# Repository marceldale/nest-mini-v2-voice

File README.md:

# Open voice satellite board for the Google Nest Mini (2nd gen)

A drop-in replacement board that turns a Google Nest Mini (2nd gen) into a fully local voice
assistant for Home Assistant. Started from the open design by
[iMike78](https://github.com/iMike78/nest-mini-drop-in-pcb) (nest-mini-drop-in-pcb,
CERN-OHL-S v2) and since then reworked, verified and extended into its own board. Everything
that was changed, and why, is in [CHANGES.md](CHANGES.md); the people and projects this one
stands on are named under [Credits](#credits).

> [!WARNING]
> **Status (5 Oct 2026): rev A2 in production at JLCPCB (2 boards, ordered 2 Oct 2026, completion
> expected around 14 Oct 2026).** Every change has been
> verified on paper only — netlist, ERC, DRC with schematic parity, datasheets, firmware source.
> The rotations of all 31 changed or new parts were checked in JLCPCB's assembly preview, and the
> board was ordered with the two fixed options (via filling, ENIG). **Nothing has been checked on
> hardware yet.** Until bring-up results are published here, **do not manufacture from these
> files.** Watch the repository for updates.

> [!NOTE]
> This status line changes again when the boards have been brought up. The steps are tracked in
> the roadmap below; the order itself is in [CHANGES.md](CHANGES.md#rev-a2-ordered-2-oct-2026).

## What it is

The Google Nest Mini (2nd gen) is a well-built little speaker: a good 40 mm driver, a
clean enclosure, two microphones and a touch surface. What ties it to Google is only the
circuit board inside.

This project replaces that board. You open the Nest Mini, take out Google's electronics
and put this board in its place. Speaker, housing, base plate and touch surface stay as
they are. What you get is a fully local voice assistant for Home Assistant: wake word,
speech and echo cancellation run on the device (ESP32-S3 + XMOS XU316), nothing leaves
your network, and the speaker still plays music and announcements.

Under the hood it follows the Home Assistant Voice Preview Edition: same processor
pair, same audio architecture, same ESPHome firmware base — fitted into the Nest Mini's
size, power and mounting constraints.

**What you need:** a Nest Mini (2nd gen), this board (assembled), a Home Assistant
installation and a USB-C cable for the ESP32. The XMOS gets its first image from the ESP32 itself
(a two-step button in Home Assistant; written and compiled, not yet run on hardware — see
Highlights), or over JTAG (J4, an XTAG4 adapter). Wi-Fi can be set up over Bluetooth (Improv,
confirmed by touching the centre button, as on Voice PE). If you
run it from USB rather than from the Nest Mini's own 14 V base plate, use a supply that can give
**1 A** — at full LED brightness the board draws up to 0.8 A, so a plain 500 mA charger is not
enough. On USB alone the amplifier has no supply — PVDD comes only from the 14 V rail (R66) — so
the speaker stays silent while microphones, LEDs and Wi-Fi work; the log then shows a PVDD
under-voltage fault or a `tas58xx` set-up error. That is expected, not a defect.

**What it is not:** a finished consumer product. It is an open hardware design at
prototype stage (see status above). No affiliation with Google.

## Highlights

* **XMOS flash written from the ESP32.** A bus switch (U16, after the Satellite1 principle) lets
  the ESP32 write the XMOS flash directly; the ESPHome component
  [`xmos_flasher`](firmware/esphome/components/xmos_flasher/README.md) does it from a two-step
  button in Home Assistant. **Written and compiled, not yet run on hardware.** JTAG stays as the
  fallback: J4 is an xSYS2 pad field, an XTAG4 plugs on 1:1. Later updates run over I²C (DFU) from
  the ESP32.

  **What the button overwrites:** the whole **1 MiB boot partition** of the XMOS flash U11 is
  erased (256 sectors) and rewritten with the factory image `firmware/xmos/ffva_v1.3.1_factory.bin`
  (286 720 bytes), checked against its MD5 and read back; everything after the image must read
  FFh. An image that a later DFU update put there is replaced by 1.3.1 as well. The data partition
  above 1 MiB is not touched, and the flash status registers are only read, never written — a
  write-protected flash is reported, not unlocked. It works on USB alone or on 14 V (all LEDs
  are switched off meanwhile; load below 0.5 A), needs the enable switch first and takes about 15 s;
  on success the ESP32 restarts.

* **Audio path as on Voice PE.** ESP32 feeds the amplifier and the echo reference on one
  line; XU316 is the clock master. Works with the unmodified Voice PE XMOS firmware.

* **Power without operating rules.** Upstream, USB-C and the 14 V supply must never be
  connected at the same time, and even USB alone back-feeds the 14 V rail through the
  buck converter (a known issue). This board adds an ideal diode (LM66100) behind the
  5 V converter and a small switch that disables the USB supply while 14 V is present.
  Result: plug in USB, 14 V or both, in any order, without risk to the board or the host
  PC.

* **XU316 core on a buck converter.** Upstream feeds the 0.9 V core from a 200 mA linear
  regulator dropping 2.4 V, while the XU316 draws about 300 mA typical and up to 1 A under
  DSP load: the regulator would overheat and the XMOS would brown out. This board uses the
  TPS62065 with 2 A. Also: touch controller wired, antenna matching at the antenna, mic-3 path removed, EasyEDA-checked
  footprints, every part with an LCSC number.

* **Expansion connector (12-pin FPC)** for an add-on ring board. We wanted more than a
  voice satellite: presence detection (radar over UART), temperature/humidity (I²C), IR
  transmit and receive for controlling TV or air conditioning, and an LED ring. None of
  this fits inside the Nest Mini housing (the mounting plate sits flush on the board), so
  the connector stays unpopulated there and the board works as a plain Nest Mini
  replacement. In a custom enclosure it connects to a ring board — LEDs, IR emitters and
  receivers, radar module — that is planned as the next project. The main board carries
  the signals, the ring board carries the sensors.

## Roadmap

- [x] Design review against upstream, Voice PE and Gen1 ([CHANGES.md](CHANGES.md))
- [x] Rev A2 schematic and layout: XMOS flash via ESP32, Voice PE audio path, power without
      operating rules, expansion connector routed
- [x] Rev A2 silkscreen: pin-1 marks, test point labels, revision and date; no DRC warnings left
- [x] Independent audit of rev A2; critical and layout-relevant findings fixed (CHANGES.md section 10)
- [x] Rev A2 manufacturing files regenerated after the audit fixes (`fertigung/`, 1 Oct 2026)
- [x] Rotation check of the 31 changed or new parts in the fabricator's assembly preview
      (JLCPCB preview, 2 Oct 2026; U18, U16, U5, Q4 corrected in the CPL beforehand, Y1 by order remark)
- [x] ESP32-side flasher for the XMOS image — written and compiled, not yet run on hardware
      (`firmware/esphome/components/xmos_flasher/`; fallback: J4 with an XTAG4)
- [x] Rev A2 ordered: 2 assembled boards (5 bare PCBs), JLCPCB, 2 Oct 2026
- [ ] Bring-up: resistance check, power rails, XMOS flash via ESP32
- [ ] Audio, microphones, echo cancellation, touch, LEDs
- [ ] Wi-Fi sensitivity against a reference device
- [ ] Firmware release (ESPHome YAML + XMOS factory image)
- [ ] Ring board and enclosure files
- [ ] Certification plan
- [ ] Crowd Supply campaign

## Trademarks

Google and Google Nest Mini are trademarks of Google LLC. This project is not affiliated with,
endorsed by or sponsored by Google. Home Assistant and ESPHome are projects of the Open Home
Foundation / Nabu Casa. XMOS and xcore are trademarks of XMOS Ltd. All trademarks belong to
their respective owners and are used here only to say what this board is compatible with.

## Licences

| What | Licence |
|---|---|
| Hardware — schematic, layout, our footprints, manufacturing data | **CERN-OHL-S v2** |
| ESPHome YAML, Python tools, documentation | **MIT** |
| XMOS firmware image under `firmware/xmos/` | **XMOS Public Licence v1** — not ours |
| ESPHome component `xmos_flasher` under `firmware/esphome/components/` | **GPL-3.0-only** for the C++ files — derived from [FutureProofHomes/Satellite1-ESPHome](https://github.com/FutureProofHomes/Satellite1-ESPHome) (`memory_flasher`, © Mischa Siekmann, commit `8f8906c`), whose `LICENSE` is the ESPHome licence: C/C++ under GPLv3 without "or any later version", Python under MIT. `__init__.py`, the README and the host test are **MIT**. See [`LICENSES/GPL-3.0-only.txt`](LICENSES/GPL-3.0-only.txt) |
| ESPHome component `tas58xx` under `firmware/esphome/components/` | **GPL-3.0-or-later** — © mrtoy-me, based on work by Andriy Malyshenko (sonocotta); patched by us (start-up order, loop bandwidth), see [`firmware/esphome/PATCH.md`](firmware/esphome/PATCH.md) |
| KiCad library excerpts in `lib_lokal/` | **CC-BY-SA-4.0**, © KiCad Libraries Contributors |
| Parts of `lib_lokal/` (vendor footprints and symbols) | **terms not established** — see below |

Full texts are in [`LICENSES/`](LICENSES/). Files that can carry a comment header do carry an
`SPDX-License-Identifier`; for KiCad documents, Gerbers and binaries the assignment is in
[`REUSE.toml`](REUSE.toml), following the [REUSE](https://reuse.software) specification.

**One honest gap**, written up in
[`LICENSES/LicenseRef-Vendor-Model-Terms-Not-Established.txt`](LICENSES/LicenseRef-Vendor-Model-Terms-Not-Established.txt):

* The vendor 3D models the board references are **not** part of this repository: we hold no
  licence document for any of them. The 3D view therefore shows those parts without a body;
  fabrication and assembly do not need them.
* Parts of `lib_lokal/` have a similar problem: ten of the 23 footprints in `Onju.pretty` carry a
  SnapEDA or EasyEDA note, `New_Library.kicad_sym` is SnapEDA, and the Seeed and reSpeaker symbols
  come from Seeed's project. They arrived with the upstream design and we pass them on unchanged.
  This directory **cannot** be left out — without it the design does not open.

**`lib_lokal/` and the two library tables are versioned on purpose.** The design references every
symbol and footprint through `${KIPRJMOD}/lib_lokal/`, so a clone without them opens with empty
placeholders. The directory holds trimmed excerpts, not whole libraries: `Device.kicad_sym` is
17 kB here against 2 374 kB in a KiCad 9.0.9 installation. KiCad's library licence grants an
exception for designs that *use* the libraries but states that it does not apply when they are
redistributed as a collection — which is what this directory does — so those files keep
CC-BY-SA-4.0 with attribution.

The C++ code in this repository is the patched copy of the ESPHome component `tas58xx`
(GPL-3.0-or-later) and the component `xmos_flasher` (GPL-3.0-only, because its source states GPLv3
without "or later"), both under `firmware/esphome/components/`; see the table above.
CERN-OHL-S v2 is a **strongly reciprocal** licence: if you make and distribute a board from
these files, or from a modified version of them, you have to make the complete source of your
version available under the same licence. See
[`LICENSES/CERN-OHL-S-2.0.txt`](LICENSES/CERN-OHL-S-2.0.txt), sections 3.2 and 4.

---

# For reference

Everything below is the technical detail — useful once you have a board in your hand, and not
needed to understand what the project is.

## Test points

Eighteen pads, all bare copper, nothing to populate. Sixteen are on the microphone side; the touch
electrodes are on the LED side. The silkscreen carries a short name next to each pad — the full net
name would not fit on a 68 mm board.

| Marking | Ref | Net | Side | Position | What you should see |
|---|---|---|---|---|---|
| `3V3` | TP1 | `+3V3` | microphone side | 163.00 / 74.50 | 3.3 V |
| `5V_SW` | TP3 | `/Power/+5V_SW` | microphone side | 121.40 / 102.00 | about 5 V, **before** the ideal diode U18 |
| `1V8` | TP4 | `+1V8` | microphone side | 145.70 / 71.50 | 1.8 V |
| `VDD` | TP5 | `VDD` | microphone side | 130.40 / 81.60 | 0.9 V |
| `3V3` | TP6 | `+3V3` | microphone side | 107.40 / 94.60 | 3.3 V |
| `XRST` | TP11 | `XU316_RST` | LED side | 126.10 / 66.50 | logic; high = XU316 held in reset |
| `MUTE` | TP12 | `MUTE` | microphone side | 140.90 / 116.80 | logic; follows the mute slider |
| `PA_EN` | TP13 | `AUDIO_PA_EN` | microphone side | 130.70 / 109.10 | logic; high = amplifier enabled |
| *(no marking)* | TP14 | `ELEC2` | LED side | 159.20 / 89.90 | touch electrode, right |
| *(no marking)* | TP15 | `ELEC1` | LED side | 135.82 / 119.53 | touch electrode, centre |
| *(no marking)* | TP16 | `ELEC0` | LED side | 114.20 / 88.90 | touch electrode, left |
| `5V` | TP17 | `+5V` | microphone side | 122.42 / 105.55 | about 5 V, **after** U18 — below TP3 by I × 79 mΩ (LM66100 R_ON): ≈ 8 mV per 100 mA, 55…65 mV at 0.7…0.8 A |
| `14V` | TP18 | `+14V` | microphone side | 143.90 / 109.43 | 14 V from the base plate |
| `RST` | TP19 | `ESP_RST` | microphone side | 118.58 / 79.30 | logic; low = ESP32 in reset |
| `BOOT` | TP20 | `ESP_BOOT` | microphone side | 121.84 / 81.75 | logic; low at power-up = boot mode |
| `GND` | TP21 | `GND` | microphone side | 120.58 / 64.74 | 0 V reference, next to U8 |
| `GND` | TP22 | `GND` | microphone side | 128.74 / 104.08 | 0 V reference, next to U14 |
| `VMIC` | TP23 | `VDD_MIC` | microphone side | 105.10 / 88.35 | 3.3 V microphone supply |

The three touch points carry no silkscreen: they sit inside the electrode rings on the LED side,
where any lettering would end up on copper. Their names are `T_R`, `T_C` and `T_L` in the schematic.

**The pair TP3 / TP17 is the one to measure first.** TP3 sits before the ideal diode U18, TP17
after it. The difference is the load current times U18's on-resistance (79 mΩ typical, LM66100 datasheet):
under 20 mV at idle, about 55…65 mV at 0.7…0.8 A; in USB-only operation TP3 should read
roughly 0 V, because the 14 V rail is then dead and the diode blocks the path back into it.

## Connectors

The board carries a designator and a pin-1 dot for every connector; the pinouts are here rather than
on the silkscreen, where they would not be legible at 0.5 mm pitch.

### J6 — ribbon cable to the LED ring board, 12 way, 0.5 mm pitch

| Pin | Net | | Pin | Net |
|---|---|---|---|---|
| 1 | `GND` | | 7 | `UART_RX` |
| 2 | `+5V` | | 8 | `I2C_SDA` |
| 3 | `+5V` | | 9 | `I2C_SCL` |
| 4 | `GND` | | 10 | `IR_TX` |
| 5 | `LED_DOUT` | | 11 | `IR_RX` |
| 6 | `UART_TX` | | 12 | `+3V3` |

Pin 1 is the one nearest the dot. `LED_DOUT` continues the LED chain from LED6 through R80, so the
ring board's first LED is index 6 as far as the firmware is concerned.

### POWER_IN1 — flat flex to the base plate, 10 way, 0.5 mm pitch

| Pin | Net | | Pin | Net |
|---|---|---|---|---|
| 1 | `GND` | | 6 | `GND` |
| 2 | `MUTE` | | 7 | `+14V` |
| 3 | `GND` | | 8 | `+14V` |
| 4 | `GND` | | 9 | `+14V` |
| 5 | `GND` | | 10 | `+14V` |

**Confirmed pin for pin against an independent design:** the schematic of
[Onju Voice](https://github.com/justLV/onju-voice) (`hardware/Onju-Home.SchDoc`, a replacement
board for the same Nest Mini 2nd gen) has the same ten-way connector as J1, and all ten pins
agree — 1 and 3–6 `GND`, 2 `MUTE`, 7–10 `14V`. Metering it on an original is optional; the quick
check is in `CHANGES.md` ("POWER_IN1: the pinout is now confirmed against a second source").

### J4 — XMOS JTAG pad field, 2×5, 1.27 mm pitch, unpopulated

The pin-out is the **xSYS2 JTAG-only header** of the XU316 datasheet (appendix G.3, figure 25), so
an XTAG4 plugs on **1:1** — pin 1 to pin 1. Pin 1 is marked by the silkscreen dot.

| Pin | Net | | Pin | Net |
|---|---|---|---|---|
| 1 | `+1V8` (VREF) | | 2 | `TMS` |
| 3 | `GND` | | 4 | `TCK` |
| 5 | `GND` | | 6 | `TDO` |
| 7 | `GND` | | 8 | `TDI` |
| 9 | `GND` | | 10 | `RST_N` |

VREF is 1.8 V on pin 1, with 100 nF (C103) right next to it. There is no 5 V and no 3.3 V on this
field. Up to the audit fixes of 1 Oct 2026 the field carried a rotated, non-standard pin-out with
VREF on pin 6; a board made from an older revision needs an adapter.

## Before bring-up

> [!NOTE]
> **Amplifier driver.** The ESPHome core component `tas58xx` (TAS5805M) arrives with ESPHome 2026.10.
> Until then use ESPHome `dev`, or the patched copy under `firmware/esphome/components/tas58xx`, which
> `nest-mini-v2-voice.yaml` loads by default and which builds with ESPHome 2026.9.0. A configuration for
> the core component is [`nest-mini-v2-voice-kerntreiber.yaml`](nest-mini-v2-voice-kerntreiber.yaml)
> (ESPHome `dev` / 2026.10 or later; it adds the 175 kHz loop bandwidth the core component does not set yet).

> [!CAUTION]
> **Do not burn `EFUSE_STRAP_JTAG_SEL` on the ESP32-S3.** Rev A2 uses GPIO3 and GPIO39 to
> GPIO42 as an SPI bus to the XMOS flash. In the factory state JTAG runs over the
> USB-Serial/JTAG controller and those pins are free; burning the eFuse switches JTAG to
> those pins and breaks the XMOS flash path. Details in
> [CHANGES.md](CHANGES.md#do-not-burn-efuse_strap_jtag_sel-esp32-s3).

## Manufacturing files

**`fertigung/` holds the rev A2 set**, generated after the audit fixes on 1 Oct 2026: Gerbers and
Excellon drill files, `gerber_jlcpcb.zip` for upload, BOM and CPL for JLCPCB, BOM and assembly
drawing for PCBWay. [`fertigung/ABLAUF.md`](fertigung/ABLAUF.md) documents the commands that
produce it and the checks each one prints — nothing in that directory is edited by hand.
**It is not released**: the board has never been fabricated, and two checks are still open (see
below).

Before ordering, these are the points to watch; the full list with the evidence is under
["Before you order" in CHANGES.md](CHANGES.md#before-you-order-the-seven-things-to-get-right):

* **0.10 mm minimum track width** for the two UART signals — fabricable at JLCPCB without a
  surcharge, but not everywhere.
* **Via-in-pad:** board vias reach into 23 pads (58 vias, all same-net), among them three signal
  pads and the large pads of U8 and U10. Order the vias **Epoxy Filled & Capped**.
* **U11 must be the `IQ` variant** of the W25Q32JV, not `IM` — the footprint cannot tell them
  apart, and only `IQ` has the QE bit set at the factory.
* Seven same-net via pairs sit exactly at the **0.2 mm hole-to-hole limit**.
* **J1** (Molex 1054500101, C134092) is stocked but flagged “process difficult” in the BOM
  check — confirm it by hand.
* Stack-up: 4 layers, 1.6 mm, **JLC04161H-7628**; surface finish chosen at order time.

Placement corrections by hand are **no longer needed**: rev A1 shipped a CPL with 19 of them, and
rev A2 fixes the footprint origins themselves instead (X1, J5, J1), so the CPL exporter
writes a correct CPL directly; the remaining nineteen corrections are applied automatically.

**Two things are still open**, both for the operator and both listed in
[`fertigung/DREHLAGEN_PRUEFEN.md`](fertigung/DREHLAGEN_PRUEFEN.md):

1. **31 parts need checking in JLCPCB's assembly preview** — those whose LCSC number changed
   since rev A1 (U5, LED2–LED5, J6, R76, R77, R80, X1, J1) or that are new (U16, U18, U19, Q4),
   nine from the audit fixes (L1, L2 with a new footprint; C20, C100 with new numbers;
   C105–C109 new, all unpolarised), and seven from the pin audit and the order (Y1 with a new number — the one
   where rotation matters, a 90° error puts the crystal on the ground pads, and it has no model in
   the preview, so the order carries the remark "Y1 orientation per silkscreen pin-1 corner mark
   (top-left)"; R72, C17, C63, C98, R35 with new numbers; R81 new). The first preview on 2 Oct 2026
   found U18 and U16 turned; a recomputation of all 42 polarised parts against the fabricator's
   footprints corrected four rotations (U18, U16, U5, Q4) — see `CHANGES.md`. C110 is not fitted and not in the CPL.
   For them the fabricator's own footprint decides the zero orientation, and that has not been
   compared yet. Everything else was checked in rev A1 and has not moved since.
2. **Two order options are fixed for this board** and have to be selected because they are not in
   the Gerbers: via covering ***Epoxy Filled & Capped*** (vias reach into 23 pads) and surface
   finish **ENIG** — decided, not optional (0.40 mm pitch, QFN thermal pads, the J4
   spring-contact field, test points and touch electrodes). Both are in "Before you order" in
   `CHANGES.md`.

The upstream design and its own documents are at
[iMike78/nest-mini-drop-in-pcb](https://github.com/iMike78/nest-mini-drop-in-pcb).

## Credits

This board exists because other people published theirs first.

* **[iMike78](https://github.com/iMike78/nest-mini-drop-in-pcb)** — *nest-mini-drop-in-pcb*,
  the design this one forks. The board outline, the mounting geometry, the microphone and touch
  arrangement and a great deal of the layout are the designer's work.
* **[Onju Voice](https://github.com/justLV/onju-voice)** (Justin Alvey) — the first drop-in
  board for the Nest Mini, and the origin of the `Onju` footprint library this project still uses.
* **[Home Assistant Voice PE](https://github.com/esphome/home-assistant-voice-pe)**
  (Nabu Casa / Open Home Foundation) — the audio architecture this board follows: the same
  ESP32-S3 + XMOS XU316 pair, the same clocking, and the XMOS firmware it runs.
* **[Satellite1](https://github.com/FutureProofHomes/Satellite1-ESPHome)** (FutureProofHomes)
  — the method for flashing the XMOS from the ESP32, which is what makes this board
  programmable without a debugger.
* **[ESPHome](https://esphome.io) and [Home Assistant](https://www.home-assistant.io)** — the
  firmware and the platform all of it runs on.

## How to follow or contribute

Star or watch the repository. **Issues and Discussions are handled here, in this repository:**
Discussions for questions, Issues for errors in the design or the documentation. Hardware
support starts after bring-up. Reference thread: Home Assistant community, topic 860001.

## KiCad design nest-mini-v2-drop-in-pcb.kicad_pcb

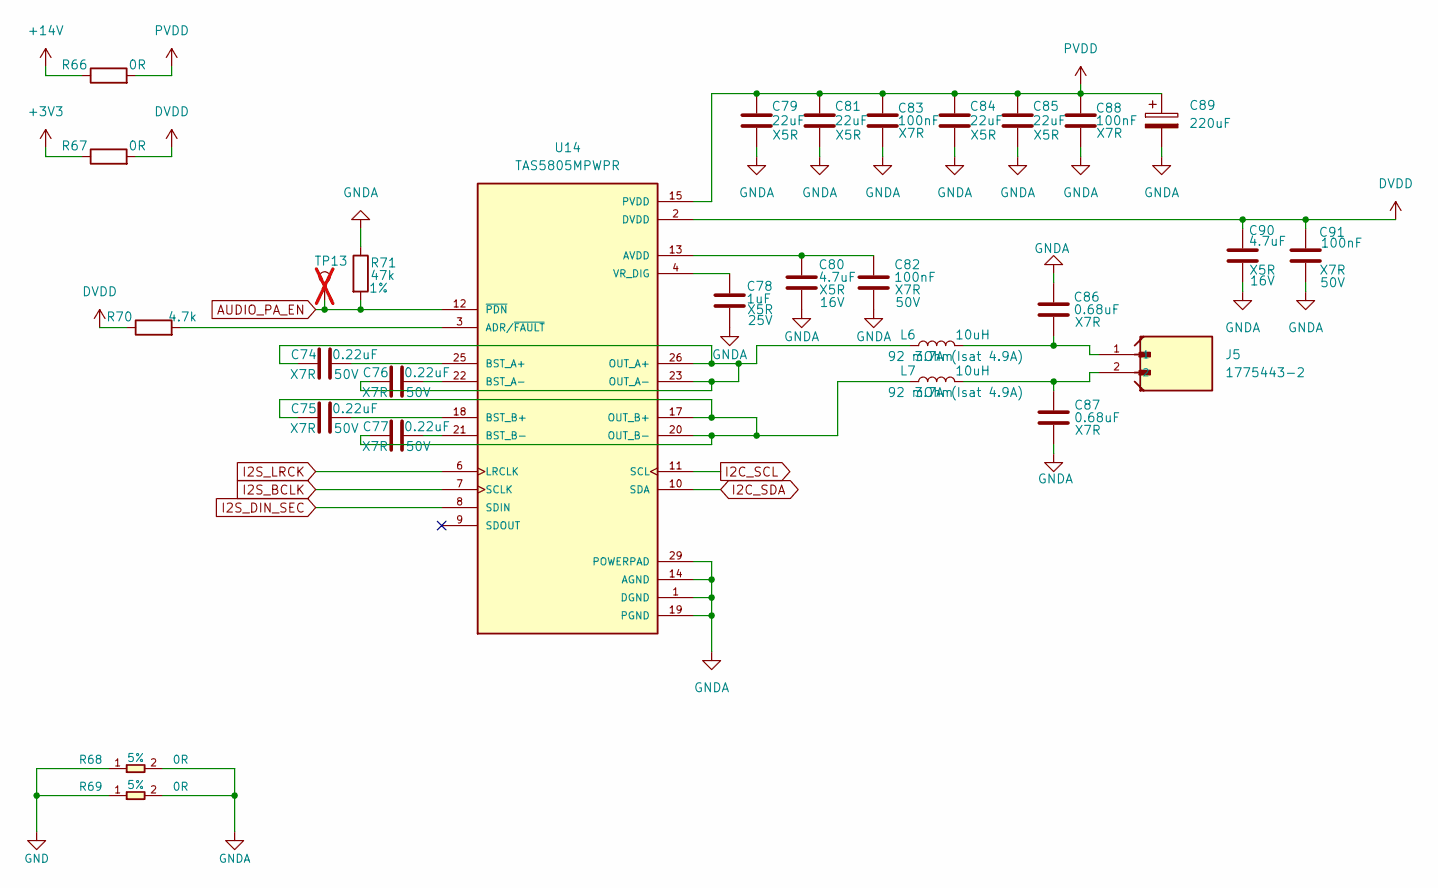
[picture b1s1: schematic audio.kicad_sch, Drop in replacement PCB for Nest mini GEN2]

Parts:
C74, C75, C76, C77: 0.22uF; C_0603_1608Metric; Voltage 50V; Manufacturer Part CC0603KRX7R9BB224; LCSC Part # C107083
C78: 1uF; C_0402_1005Metric; Voltage 25V; Manufacturer Part CL05A105KA5NQNC; LCSC Part # C52923
C79, C81, C84, C85: 22uF; C_0805_2012Metric; Voltage 25V; Manufacturer Part CL21A226MAQNNNE; LCSC Part # C45783
C80, C90: 4.7uF; C_0603_1608Metric; Voltage 16V; MPN CL10A475KO8NNNC; LCSC Part # C19666
C82, C91: 100nF; C_0603_1608Metric; Voltage 50V; Manufacturer Part CC0603KRX7R9BB104; LCSC Part # C14663
C83, C88: 100nF; C_0402_1005Metric; Voltage 50V; Manufacturer Part CL05B104KB54PNC; LCSC Part # C307331
C86, C87: 0.68uF; C_0805_2012Metric; Voltage 50V; Manufacturer Part CC0805KKX7R9BB684; LCSC Part # C107133
C89: 220uF; C_Elec_6.3x7.7; Voltage 25V; Manufacturer Part MA25V220M6X8; LCSC Part # C46550464
J5: 1775443-2; PARTREV B5; LCSC Part # C5162845
L6, L7: 10uH; MTQH404030S100MBT; Manufacturer Part MTQH404030S100MBT; LCSC Part # C51883185
R66: 0R; R_1206_3216Metric; Manufacturer Part 1206W4F0000T5E; LCSC Part # C17888
R67: 0R; R_0603_1608Metric; Manufacturer Part 0603WAF0000T5E; LCSC Part # C21189
R68, R69: 0R; R_0805_2012Metric; Tolerance 5%; MPN 0805W8F0000T5E; LCSC Part # C17477
R70: 4.7k; R_0402_1005Metric; Tolerance 5%; Manufacturer Part 0402WGF4701TCE; LCSC Part # C25900
R71: 47k; R_0402_1005Metric; Tolerance 1%; Manufacturer Part 0402WGF4702TCE; LCSC Part # C25792
TP13: PA_EN; TestPoint_Pad_D1.0mm; not fitted
U14: TAS5805MPWPR; Manufacturer Part TAS5805MPWPR; LCSC Part # C478472

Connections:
+3V3: R67.1; also elsewhere on the board
+14V: R66.1; also elsewhere on the board
AUDIO_PA_EN: R71.2, TP13.1, U14.12 (~PDN); also elsewhere on the board
DVDD: C90.1, C91.1, R67.2, R70.1, U14.2 (DVDD)
GND: R68.1, R69.1; also elsewhere on the board
GNDA: C78.2, C79.2, C80.2, C81.2, C82.2, C83.2, C84.2, C85.2, C86.2, C87.2, C88.2, C89.2, C90.2, C91.2, R68.2, R69.2, R71.1, U14.1 (DGND), U14.5 (DGND), U14.14 (AGND), U14.19 (PGND), U14.24 (PGND), U14.29 (POWERPAD), U14.30 (POWERPAD), U14.31 (POWERPAD), U14.32 (POWERPAD), U14.33 (POWERPAD), U14.34 (POWERPAD), U14.35 (POWERPAD), U14.36 (POWERPAD), U14.37 (POWERPAD), U14.38 (POWERPAD), U14.39 (POWERPAD), U14.40 (POWERPAD), U14.41 (POWERPAD), U14.42 (POWERPAD), U14.43 (POWERPAD), U14.44 (POWERPAD), U14.45 (POWERPAD), U14.46 (POWERPAD), U14.47 (POWERPAD), U14.48 (POWERPAD), U14.49 (POWERPAD), U14.50 (POWERPAD), U14.51 (POWERPAD), U14.52 (POWERPAD), U14.53 (POWERPAD)
I2C_SCL: U14.11 (SCL); also elsewhere on the board
I2C_SDA: U14.10 (SDA); also elsewhere on the board
I2S_BCLK: U14.7 (SCLK); also elsewhere on the board
I2S_DIN_SEC: U14.8 (SDIN); also elsewhere on the board
I2S_LRCK: U14.6 (LRCLK); also elsewhere on the board
unnamed: C86.1, J5.1, L6.2
unnamed: C87.1, J5.2, L7.2
unnamed: R70.2, U14.3 (ADR/~FAULT)
unnamed: C80.1, C82.1, U14.13 (AVDD)
unnamed: C74.2, U14.25 (BST_A+)
unnamed: C76.2, U14.22 (BST_A-)
unnamed: C75.2, U14.18 (BST_B+)
unnamed: C77.2, U14.21 (BST_B-)
unnamed: C74.1, C76.1, L6.1, U14.23 (OUT_A-), U14.26 (OUT_A+)
unnamed: C75.1, C77.1, L7.1, U14.17 (OUT_B+), U14.20 (OUT_B-)
unnamed: C78.1, U14.4 (VR_DIG)
PVDD: C79.1, C81.1, C83.1, C84.1, C85.1, C88.1, C89.1, R66.2, U14.15 (PVDD), U14.16 (PVDD), U14.27 (PVDD), U14.28 (PVDD)

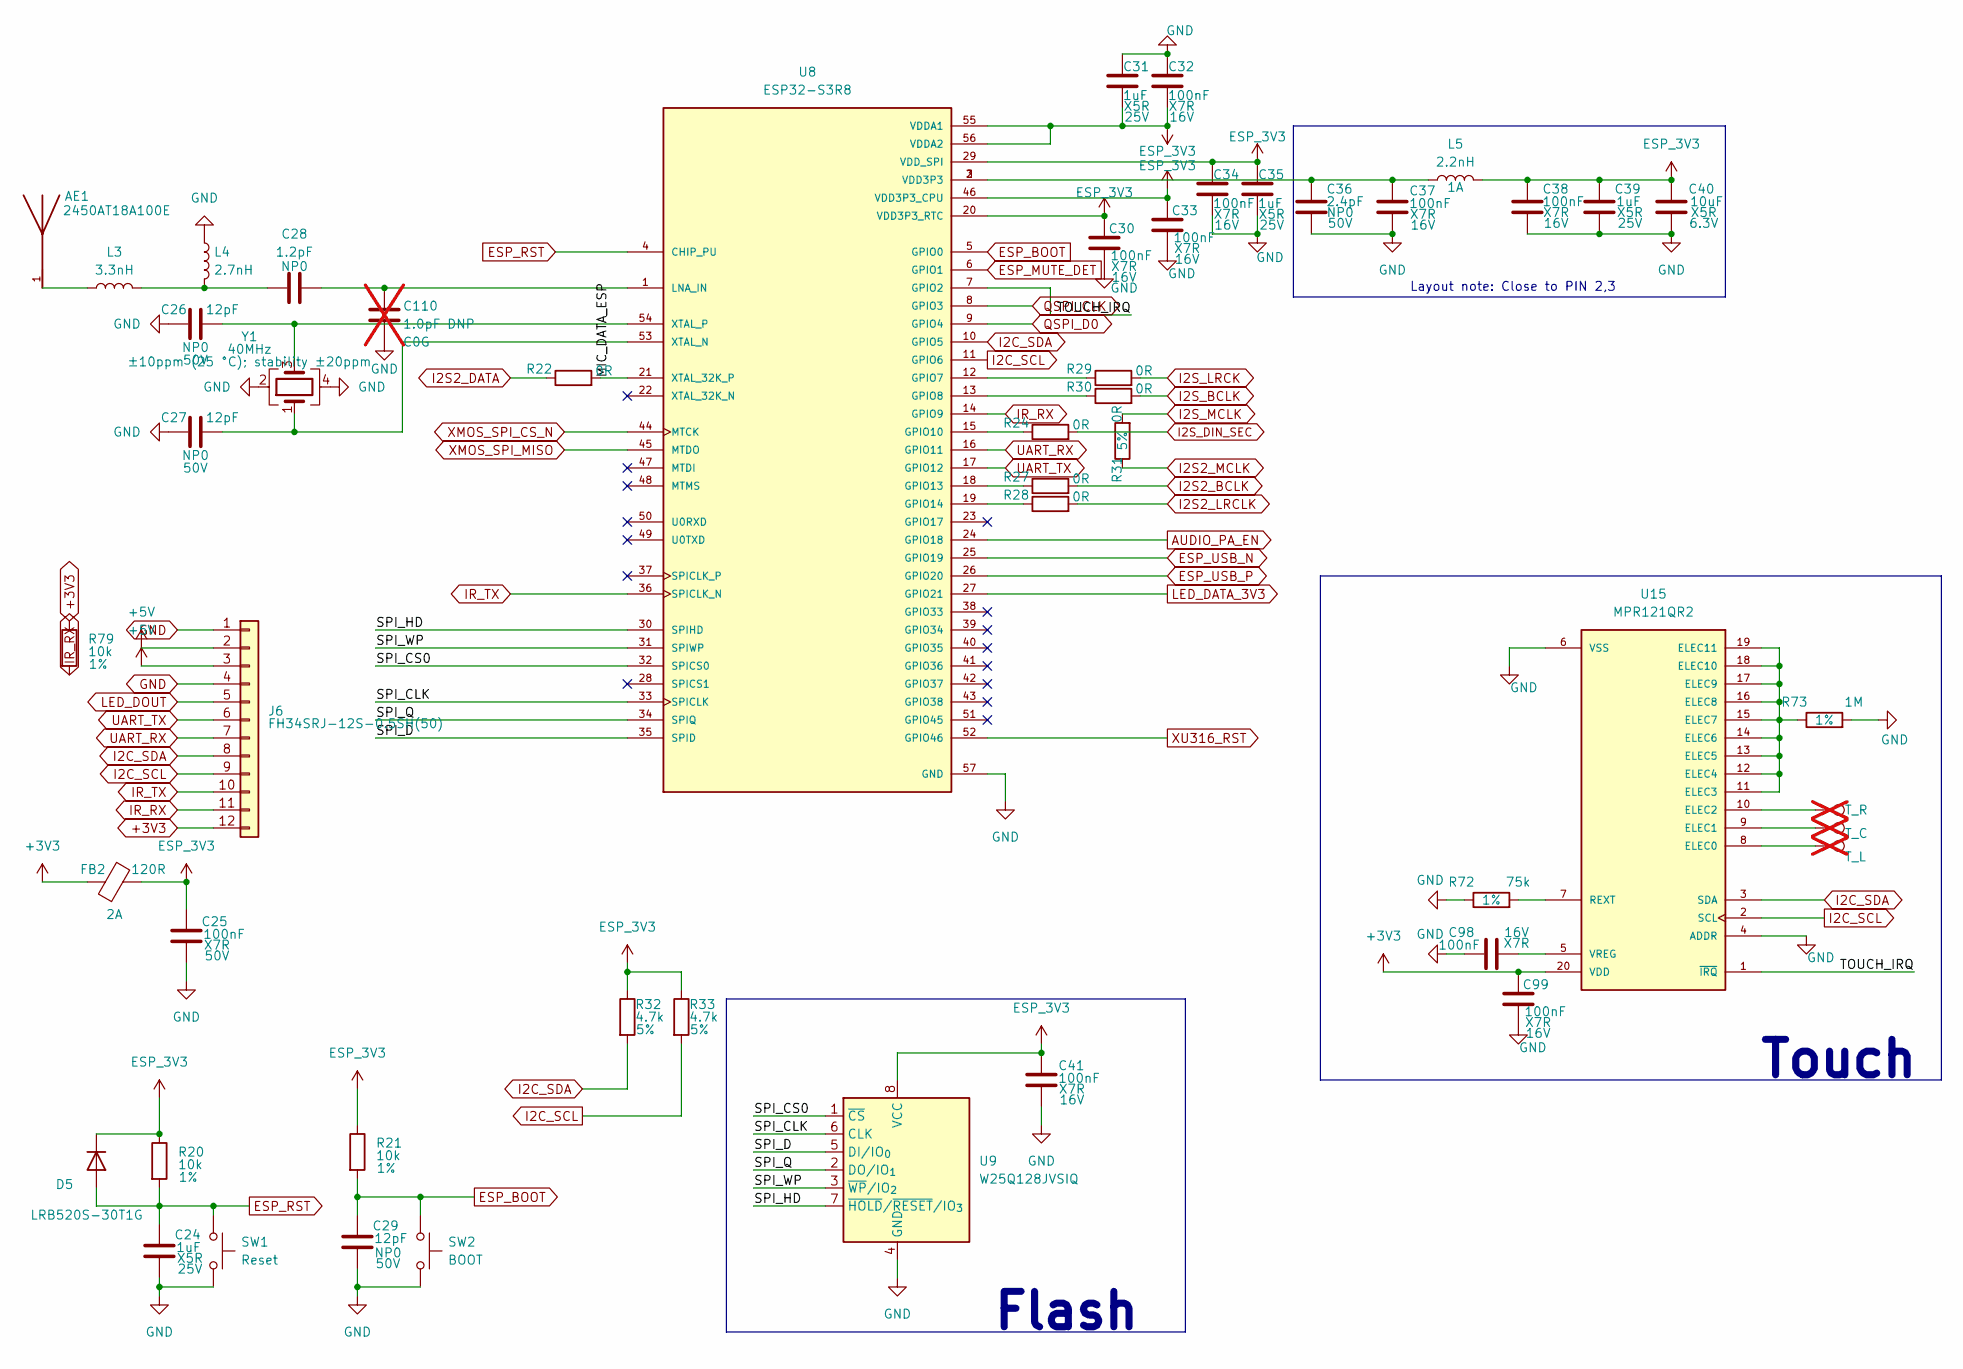
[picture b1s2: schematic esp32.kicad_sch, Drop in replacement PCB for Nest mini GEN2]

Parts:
AE1: 2450AT18A100E; Johanson_2450AT18x100; PARTREV 1.3; LCSC Part # C89334
C24, C31, C35, C39: 1uF; C_0402_1005Metric; Voltage 25V; Manufacturer Part CL05A105KA5NQNC; LCSC Part # C52923
C25: 100nF; C_0603_1608Metric; Voltage 50V; Manufacturer Part CC0603KRX7R9BB104; LCSC Part # C14663
C26, C27, C29: 12pF; C_0402_1005Metric; Voltage 50V; Manufacturer Part 0402CG120J500NT; LCSC Part # C1547
C28: 1.2pF; C_0402_1005Metric; Voltage 50V; Manufacturer Part CC0402BRNPO9BN1R2; LCSC Part # C327292
C30, C32, C33, C34, C37, C38, C41, C98, C99: 100nF; C_0402_1005Metric; Voltage 16V; Manufacturer Part CL05B104KO5NNNC; LCSC Part # C1525
C36: 2.4pF; C_0402_1005Metric; Voltage 50V; Manufacturer Part 0402CG2R4C500NT; LCSC Part # C48346
C40: 10uF; C_0402_1005Metric; Voltage 6.3V; Manufacturer Part CL05A106MQ5NUNC; LCSC Part # C15525
C110: 1.0pF DNP; C_0201_0603Metric; Voltage 50V; Manufacturer Part GRM0335C1H1R0BA01D; LCSC Part # C85893; not fitted
D5: LRB520S-30T1G; D_SOD-523; Manufacturer Part LRB520S-30T1G; LCSC Part # C83680
FB2: 120R; BLM18PG121SN1D; Part number BLM18PG121SN1D; LCSC Part # C14709
J6: FH34SRJ-12S-0.5SH(50); HRS_FH34SRJ-12S-0.5SH_50_; Manufacturer Part FH34SRJ-12S-0.5SH(50); LCSC C424659
L3: 3.3nH; L_0402_1005Metric; Manufacturer Part SDCL1005C3N3STDF; LCSC Part # C16526
L4: 2.7nH; L_0402_1005Metric; Manufacturer Part MHQ1005P2N7BT000; LCSC Part # C434826
L5: 2.2nH; L_0402_1005Metric; Manufacturer Part LQG15HS2N2B02D; LCSC Part # C162540
R20, R21: 10k; R_0402_1005Metric; Tolerance 1%; Manufacturer Part 0402WGF1002TCE; LCSC Part # C25744
R22, R24, R27, R28, R29, R30, R31: 0R; R_0402_1005Metric; Tolerance 5%; Manufacturer Part 0402WGF0000TCE; LCSC Part # C17168
R32, R33: 4.7k; R_0402_1005Metric; Tolerance 5%; Manufacturer Part 0402WGF4701TCE; LCSC Part # C25900
R72: 75k; R_0402_1005Metric; Tolerance 1%; Manufacturer Part 0402WGF7502TCE; LCSC Part # C25798
R73: 1M; R_0402_1005Metric; Tolerance 1%; Manufacturer Part 0402WGF1004TCE; LCSC Part # C26083
R79: 10k; R_0402_1005Metric; Tolerance 1%; Manufacturer Part 0402WGF1002TCE; LCSC C25744
SW1: Reset; SW-SMD_4P-L4.2-W3.2-P2.15-LS4.5; Manufacturer Part PTS810SJS250SMTRLFS; LCSC Part # C221897
SW2: BOOT; SW-SMD_4P-L4.2-W3.2-P2.15-LS4.5; Manufacturer Part PTS810SJS250SMTRLFS; LCSC Part # C221897
TP14: T_R; TestPoint_Pad_2.5x2.5mm; not fitted
TP15: T_C; TestPoint_Pad_2.5x2.5mm; not fitted
TP16: T_L; TestPoint_Pad_2.5x2.5mm; not fitted
U8: ESP32-S3R8; QFN40P700X700X90-57N; Manufacturer Part ESP32-S3R8; LCSC Part # C2913194
U9: W25Q128JVSIQ; SOIC-8_5.3x5.3mm_P1.27mm; Manufacturer Part W25Q128JVSIQ; LCSC Part # C97521
U15: MPR121QR2; MPN MPR121QR2; LCSC Part # C91322
Y1: 40MHz; Crystal_SMD_2016-4Pin_2.0x1.6mm; Tolerance ±10ppm (25 °C); stability ±20ppm; Manufacturer Part Y201640MDBCX; LCSC Part # C49158179

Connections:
+3V3: C99.1, FB2.1, J6.12, R79.1, U15.20 (VDD); also elsewhere on the board
+5V: J6.2, J6.3; also elsewhere on the board
/ESP32-S3R8/MIC_DATA_ESP: R22.2, U8.21 (XTAL_32K_P)
/ESP32-S3R8/SPI_CLK: U8.33 (SPICLK), U9.6 (CLK)
/ESP32-S3R8/SPI_CS0: U8.32 (SPICS0), U9.1 (~CS)
/ESP32-S3R8/SPI_D: U8.35 (SPID), U9.5 (DI/IO_{0})
/ESP32-S3R8/SPI_HD: U8.30 (SPIHD), U9.7 (~HOLD/~RESET/IO_{3})
/ESP32-S3R8/SPI_Q: U8.34 (SPIQ), U9.2 (DO/IO_{1})
/ESP32-S3R8/SPI_WP: U8.31 (SPIWP), U9.3 (~WP/IO_{2})
/ESP32-S3R8/TOUCH_IRQ: U8.7 (GPIO2), U15.1 (~IRQ)
AUDIO_PA_EN: U8.24 (GPIO18); also elsewhere on the board
ESP_3V3: C25.1, C30.1, C31.2, C32.2, C33.1, C34.1, C35.1, C38.1, C39.1, C40.1, C41.1, D5.1 (K), FB2.2, L5.2, R20.1, R21.1, R32.1, R33.1, U8.20 (VDD3P3_RTC), U8.29 (VDD_SPI), U8.46 (VDD3P3_CPU), U8.55 (VDDA1), U8.56 (VDDA2), U9.8 (VCC); also elsewhere on the board
ESP_BOOT: C29.1, R21.2, SW2.1, U8.5 (GPIO0); also elsewhere on the board
ESP_MUTE_DET: U8.6 (GPIO1); also elsewhere on the board
ESP_RST: C24.1, D5.2 (A), R20.2, SW1.1, U8.4 (CHIP_PU); also elsewhere on the board
ESP_USB_N: U8.25 (GPIO19); also elsewhere on the board
ESP_USB_P: U8.26 (GPIO20); also elsewhere on the board
GND: C24.2, C25.2, C26.1, C27.1, C29.2, C30.2, C31.1, C32.1, C33.2, C34.2, C35.2, C36.2, C37.2, C38.2, C39.2, C40.2, C41.2, C98.1, C99.2, C110.2, J6.1, J6.4, L4.1, R72.1, R73.2, SW1.2, SW2.2, U8.57 (GND), U9.4 (GND), U15.4 (ADDR), U15.6 (VSS), Y1.2, Y1.4; also elsewhere on the board
I2C_SCL: J6.9, R33.2, U8.11 (GPIO6), U15.2 (SCL); also elsewhere on the board
I2C_SDA: J6.8, R32.2, U8.10 (GPIO5), U15.3 (SDA); also elsewhere on the board
I2S2_BCLK: R27.2; also elsewhere on the board
I2S2_DATA: R22.1; also elsewhere on the board
I2S2_LRCLK: R28.2; also elsewhere on the board
I2S2_MCLK: R31.1; also elsewhere on the board
I2S_BCLK: R30.2; also elsewhere on the board
I2S_DIN_SEC: R24.2; also elsewhere on the board
I2S_LRCK: R29.2; also elsewhere on the board
I2S_MCLK: R31.2; also elsewhere on the board
IR_RX: J6.11, R79.2, U8.14 (GPIO9)
IR_TX: J6.10, U8.36 (SPICLK_N)
LED_DATA_3V3: U8.27 (GPIO21); also elsewhere on the board
LED_DOUT: J6.5; also elsewhere on the board
unnamed: AE1.1, L3.1
unnamed: C28.1, L3.2, L4.2
unnamed: C36.1, C37.1, L5.1, U8.2 (VDD3P3), U8.3 (VDD3P3)
unnamed: R29.1, U8.12 (GPIO7)
unnamed: R30.1, U8.13 (GPIO8)
unnamed: R24.1, U8.15 (GPIO10)
unnamed: R27.1, U8.18 (GPIO13)
unnamed: R28.1, U8.19 (GPIO14)
unnamed: C28.2, C110.1, U8.1 (LNA_IN)
unnamed: C27.2, U8.53 (XTAL_N), Y1.1
unnamed: C26.2, U8.54 (XTAL_P), Y1.3
unnamed: TP16.1, U15.8 (ELEC0)
unnamed: TP15.1, U15.9 (ELEC1)
unnamed: TP14.1, U15.10 (ELEC2)
unnamed: R73.1, U15.11 (ELEC3), U15.12 (ELEC4), U15.13 (ELEC5), U15.14 (ELEC6), U15.15 (ELEC7), U15.16 (ELEC8), U15.17 (ELEC9), U15.18 (ELEC10), U15.19 (ELEC11)
unnamed: R72.2, U15.7 (REXT)
unnamed: C98.2, U15.5 (VREG)
QSPI_CLK: U8.8 (GPIO3); also elsewhere on the board
QSPI_D0: U8.9 (GPIO4); also elsewhere on the board
UART_RX: J6.7, U8.16 (GPIO11)
UART_TX: J6.6, U8.17 (GPIO12)
XMOS_SPI_CS_N: U8.44 (MTCK); also elsewhere on the board
XMOS_SPI_MISO: U8.45 (MTDO); also elsewhere on the board
XU316_RST: U8.52 (GPIO46); also elsewhere on the board

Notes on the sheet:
Touch
Layout note: Close to PIN 2,3
Flash

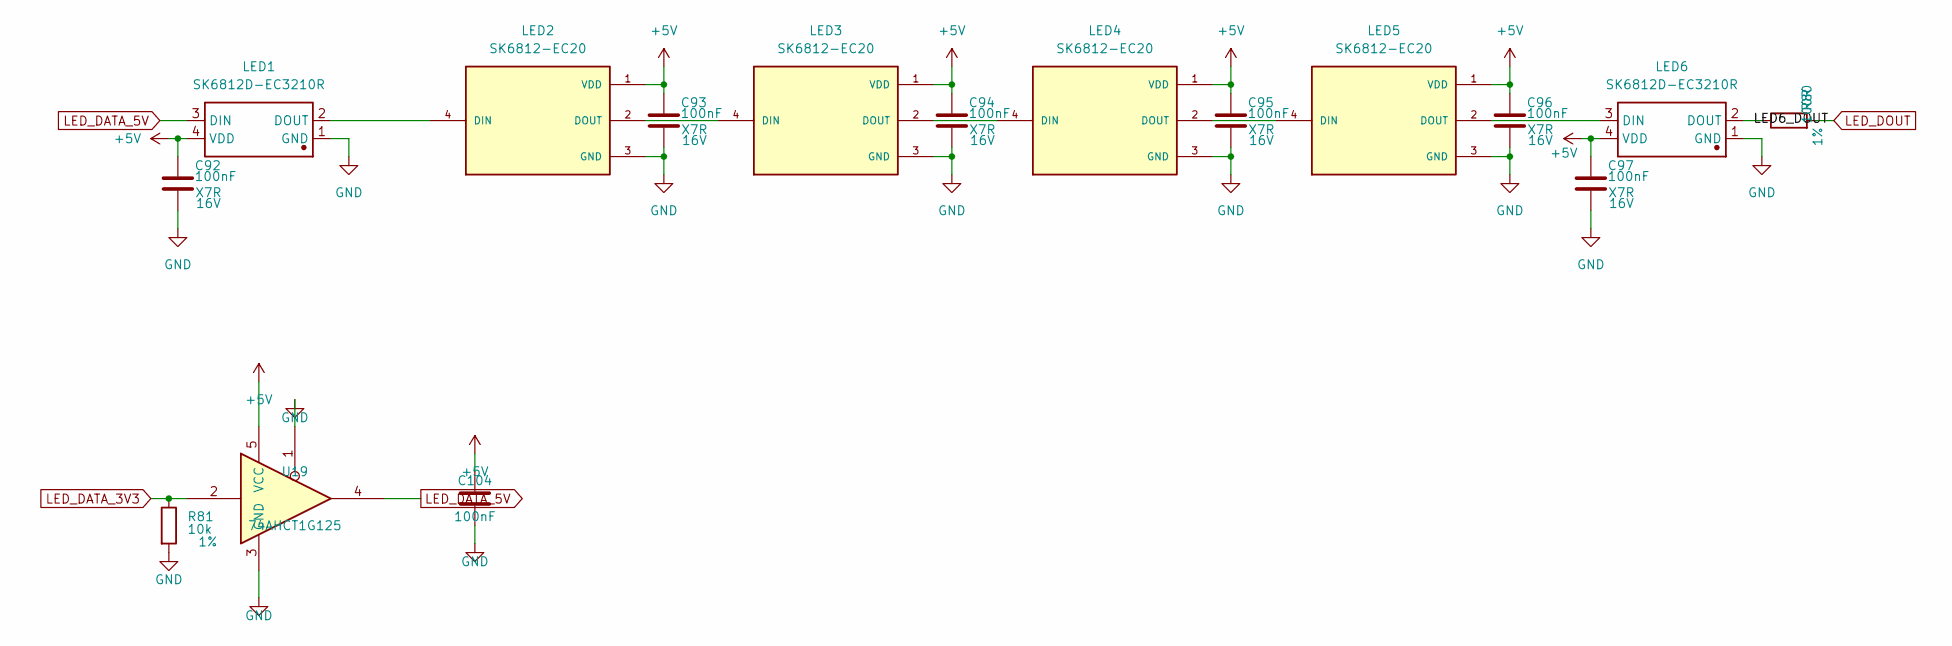
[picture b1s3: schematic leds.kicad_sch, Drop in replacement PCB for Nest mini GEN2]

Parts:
C92, C93, C94, C95, C96, C97: 100nF; C_0402_1005Metric; Voltage 16V; LCSC Part # C1525
C104: 100nF; C_0402_1005Metric; Manufacturer Part CL05B104KO5NNNC; LCSC Part # C1525
LED1, LED6: SK6812D-EC3210R; LED-SMD_4P_SK6812D-EC3210R; Manufacturer Part SK6812D-EC3210R; LCSC Part # C2890041
LED2, LED3, LED4, LED5: SK6812-EC20; SK6805-EC20; Manufacturer Part SK6812-EC20; LCSC Part # C2909058
R80: 100R; R_0402_1005Metric; Tolerance 1%; Manufacturer Part 0402WGF1000TCE; LCSC C25076
R81: 10k; R_0402_1005Metric; Tolerance 1%; Manufacturer Part 0402WGF1002TCE; LCSC C25744
U19: 74AHCT1G125; SOT-353_SC-70-5; Manufacturer Part 74AHCT1G125GW,125; LCSC Part # C12495

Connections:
+5V: C92.1, C93.1, C94.1, C95.1, C96.1, C97.1, C104.1, LED1.4 (VDD), LED2.1 (VDD), LED3.1 (VDD), LED4.1 (VDD), LED5.1 (VDD), LED6.4 (VDD), U19.5 (VCC); also elsewhere on the board
/LEDs/LED6_DOUT: LED6.2 (DOUT), R80.1
GND: C92.2, C93.2, C94.2, C95.2, C96.2, C97.2, C104.2, LED1.1 (GND), LED2.3 (GND), LED3.3 (GND), LED4.3 (GND), LED5.3 (GND), LED6.1 (GND), R81.2, U19.1, U19.3 (GND); also elsewhere on the board
LED_DATA_3V3: R81.1, U19.2; also elsewhere on the board
LED_DATA_5V: LED1.3 (DIN), U19.4
LED_DOUT: R80.2; also elsewhere on the board
unnamed: LED1.2 (DOUT), LED2.4 (DIN)
unnamed: LED2.2 (DOUT), LED3.4 (DIN)
unnamed: LED3.2 (DOUT), LED4.4 (DIN)
unnamed: LED4.2 (DOUT), LED5.4 (DIN)
unnamed: LED5.2 (DOUT), LED6.3 (DIN)

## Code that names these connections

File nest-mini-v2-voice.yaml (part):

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
# Pin-Audit U8-B6: auf der Platine belegt, in dieser Firmware absichtlich ungenutzt (Reserve, nach
# Reset hochohmig):
#   GPIO3  QSPI_CLK, GPIO4 QSPI_D0   -> XU316-Boot-Flash U11, nie treiben (siehe U10-B7)
#   GPIO39 XMOS_SPI_CS_N, GPIO40 XMOS_SPI_MISO -> ueber U16, nur bei XU316_RST = 1 durchgeschaltet
#   GPIO9  IR_RX (R79 10k Pull-up), GPIO48 IR_TX, GPIO11 UART_RX, GPIO12 UART_TX -> J6 (Erweiterung)
# XMOS-Update: I2C-DFU ueber voice_kit; Erstprogrammierung XU316: JTAG J4 (firmware/xmos/README.md).
esp32:
  board: esp32-s3-devkitc-1
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
i2c:
  - id: internal_i2c
    sda: GPIO5
    scl: GPIO6
    frequency: 400kHz

psram:
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#     30.09.2026 - der Hub nimmt nur address, id, touch_debounce, release_debounce,
#     touch_threshold, release_threshold); sie fragt den Baustein ueber I2C ab.
#     Kanaele: 0 = links (ELEC0, TOUCH_L), 1 = Mitte (ELEC1, TOUCH_C),
#     2 = rechts (ELEC2, TOUCH_R). Vorher esp32_touch auf GPIO2/3/4 (a4db7a09) -
#     GPIO2 ist jetzt TOUCH_IRQ und darf nicht als Touch-Pin laufen.
#
#     Befund 11: Der IRQ des MPR121 ist ein Open-Collector-Ausgang und hat auf der
#     Platine keinen Pull-up - in Gen1 genauso (dort `/ESP32-S3R8/TOUCH_IRQ` = U2.1
#     und U6.7, ohne Widerstand). Ohne Pull-up bliebe GPIO2 ein offener Eingang.
#     Der interne Pull-up des ESP32-S3 uebernimmt das: R_PU typisch **45 kOhm**
#     (ESP32-S3 Series Datasheet v2.2, Tabelle 5-4 "DC Characteristics", S. 65).
#     Der Sensor unten dient nur dazu, diesen Pull-up zu setzen; ausgewertet wird
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      name: "Endstufe Temperaturwarnung"
    over_temp_shutdown:
      name: "Endstufe Uebertemperatur"
  # Befund 11: haelt GPIO2 (TOUCH_IRQ) ueber den internen Pull-up auf definiertem
  # Pegel. Der MPR121-IRQ zieht aktiv nach Masse, gibt High aber nur passiv frei.
  - platform: gpio
    id: touch_irq
    internal: true
    pin:
      number: GPIO2
      mode:
        input: true
        pullup: true
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    id: hardware_mute_switch
    internal: true
    pin:
      # F2: Der Mute-Schalter meldet sich auf GPIO1 (ESP_MUTE_DET, ueber D6 von
      #     U12.2Y). R58 zieht die Leitung bereits nach ESP_3V3 hoch, ein zweiter
      #     Pull-Up im Baustein ist unnoetig. GPIO33 ist unbeschaltet.
      # D3: Polaritaet geklaert, KEIN 'inverted:' noetig. Laut Schaltplan gilt:
      #     MUTE_ON hoch = stumm; Q3 schaltet dann VDD_MIC ab,
      #     und ESP_MUTE_DET geht ueber D6 ebenfalls hoch. Hoher Pegel an GPIO1
      #     heisst also stumm - genau die Bedeutung, die on_press erwartet.
      number: GPIO1
      mode: INPUT
    on_press:
      # Play mute on sound only if software mute isn't enabled
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light:
  # Hardware LED ring. Not used because remapping needed
  #
  # F7.3 (30.09.2026): GPIO21 treibt seit rev A2 **nicht mehr** LED1 unmittelbar, sondern
  #   U19 (74AHCT1G125GW, SOT-353, LCSC C12495) als Pegelwandler auf 5 V. Netze:
  #   GPIO21 -> LED_DATA_3V3 -> U19.2 (A); U19.4 (Y) -> LED_DATA_5V -> LED1.3 (DIN).
  #   OE liegt fest auf GND, VCC auf +5V mit C104 (100 nF).
  #   Grund (Befund 10): SK6805/SK6812 fordern VIH = 0,7 x VDD, bei 5 V also 3,5 V; der
  #   ESP32-S3 sichert nur VOH >= 0,8 x VDD = 2,64 V zu. Der AHCT-Eingang nimmt 2,0 V
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  #   Wandler ist nicht invertierend, Zeitverhalten und Datenrichtung bleiben gleich.
  - platform: esp32_rmt_led_strip
    id: leds_internal
    pin: GPIO21
    # K-B3 (Pin-Audit 01.10.2026): eigene Zeiten statt chipset: SK6812. ESPHome setzt fuer
    # SK6812 T1H = 600 ns (esp32_rmt_led_strip/light.py Z. 46), die LEDs verlangen mehr:
    #   SK6812-EC20 (LED2..LED5):     T0H 0,20-0,40 | T0L >= 0,70 | T1H >= 0,70 | T1L >= 0,20 us
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voice_kit:
  id: voice_kit_component
  i2c_id: internal_i2c
  # C7 (Weg 2, 21.09.2026): XU316_RST liegt an GPIO46 (U8.52 -> R47 100R ->
  #     Gate Q2 LBSS138 -> RST_N des XU316; GPIO high = XU316 im Reset).
  #     Schaltplan an das vorhandene Layout angeglichen; GPIO17 (U8.23) ist frei:
  #     am rechten ESP32-Rand ist fuer GPIO17 und AUDIO_PA_EN (GPIO18) nur ein
  #     Via-Platz frei.
  #     GPIO46 ist Strapping-Pin (ESP32-S3 Datenblatt v2.2, Tab. 3-1: interner
  #     Pull-down, Bitwert 0; Tab. 3-3: nur GPIO0=1/beliebig und GPIO0=0/GPIO46=0
  #     sind Boot-Modi). Extern haengt an GPIO46 nur R47 und dahinter R48 470k
  #     nach GND - kein Pull-up, der Pin liest beim Reset 0. Ausgang ist
  #     moeglich (Tab. 2-4 IO MUX, S. 22: GPIO46 I/O/T).
  reset_pin:
    number: GPIO46
    # Auch xmos_flasher schaltet GPIO46 (Reset des XU316 und Busumschalter U16 haengen an
    # demselben Netz XU316_RST).
    allow_other_uses: true
  firmware:
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
# Bus-Flasher fuer den XU316 (firmware/esphome/components/xmos_flasher, Herkunft Satellite1-ESPHome).
# Schreibt das Werksabbild in U11, wenn dieser leer oder beschaedigt ist; danach Neustart, voice_kit
# liest die Version und haelt sie per DFU aktuell. Bus: CLK GPIO3 und D0 GPIO4 fest am XU316-QSPI,
# CS_N GPIO39 und MISO GPIO40 ueber U16; GPIO46 hoch = XU316 im Reset und U16 auf den ESP32.
xmos_flasher:
  id: xmos_flasher_component
  image_file: firmware/xmos/ffva_v1.3.1_factory.bin
  md5_file: firmware/xmos/MD5SUMS
  reset_pin:
    number: GPIO46
    allow_other_uses: true
  frequency: 4MHz
  progress:
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        format: "XMOS-Flash fehlgeschlagen (Status-Sensor nennt die Stelle)"

external_components:
  # Pin-Audit U10-B7: GPIO3 und GPIO4 haengen ohne Trennung an QSPI_CLK und QSPI_D0 des
  # XU316 (U16 schaltet nur CS und D1). Beide muessen in dieser Datei unbenutzt bleiben
  # (hochohmig), sonst stoeren sie Boot und Flashzugriff des XU316. Die Voice PE nutzt
  # GPIO3 fuer den Stummschalter - nicht uebernehmen.
  - source:
      type: git
      url: https://github.com/esphome/home-assistant-voice-pe
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    i2c_id: internal_i2c
    address: 0x2C          # B1: R70 legt ADR auf 0x2C; der Baustein setzt sonst 0x2D
    tas58xx_dac: TAS5805M
    enable_pin: GPIO18     # AUDIO_PA_EN -> U14.12 /PDN
    # K-B5 (Pin-Audit 01.10.2026): erst nach voice_kit einrichten. tas58xx hat
    # Prioritaet IO (900, tas58xx.h Z. 28), voice_kit HARDWARE - 1 (799, voice_kit.h
    # Z. 130) - bisher wurde der DSP freigegeben und danach der XU316 (Taktquelle)
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i2s_audio:
  - id: i2s_output
    # E5d (28.09.2026) kehrt den Datenweg von C3 um: U14.8 (SDIN) haengt jetzt am
    #     Netz I2S_DIN_SEC, also unmittelbar an GPIO10 des ESP32. Der Weg ist
    #     GPIO10 -> R24 -> I2S_DIN_SEC -> U14.8 (SDIN) und, an derselben Leitung,
    #     -> R40 -> X1D00 in den XU316 als Bezug fuer die Echoausloeschung.
    #     X1D34 (U10.53) treibt seitdem kein Ziel mehr; R25 ist seit E5c-P5 entfernt.
    #     Die Takte kommen weiter aus dem XU316 (C1: X1D01 -> I2S_LRCK,
    #     C2: X1D10 -> I2S_BCLK); nur die Datenleitung ist umgehaengt.
    # C5: Der XU316 ist Taktgeber, der ESP32 bleibt auf beiden Bussen secondary.
    # C6: Kein MCLK-Pin erklaert - am Knoten I2S_MCLK darf nur eine Seite treiben.
    #     R23 und R26 gibt es in rev A2 nicht mehr: I2S_MCLK laeuft nur innerhalb des
    #     XU316 (X1D11 -> R31 -> R44 -> X0D36), der ESP32 haengt nicht daran.
    i2s_lrclk_pin:
      number: GPIO7
    i2s_bclk_pin:
      number: GPIO8

  - id: i2s_input
    # data line is GPIO15
    i2s_lrclk_pin:
      number: GPIO14
    i2s_bclk_pin:
      number: GPIO13

microphone:
  - platform: i2s_audio
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    # E5d: 48 kHz und 32 Bit, damit der Bustakt zum TAS5805M passt.
    sample_rate: 48000
    i2s_mode: secondary
    i2s_dout_pin: GPIO10
    bits_per_sample: 32bit
    i2s_audio_id: i2s_output
    dac_type: external
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

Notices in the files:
nest-mini-v2-voice.yaml:
SPDX-FileCopyrightText: 2026 marceldale
SPDX-License-Identifier: MIT
Lizenz: GPL-3.0-or-later (Upstream-README: Grundlage ist GPL-3.0-Code von Andriy
Lizenz des Bausteins: GPL-3.0-or-later, siehe external_components und REUSE.toml.
nest-mini-v2-drop-in-pcb.kicad_pcb:
based on MiciMike Nest Mini v2 by iMike78 · CERN-OHL-S 2.0 · modified
